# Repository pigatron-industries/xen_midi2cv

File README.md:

# MIDI - CV

MIDI to control voltage converter.

Uses [PJRC Teensy 4.0](https://www.pjrc.com/teensy-4-0/) and [MikroElektronika PIXI Click](https://www.mikroe.com/pixi-click) for IO.

## Hardware

Hardware functions are split into various PCBs.

* PGTNX05 Mainboard - Contains the Teensy 4 CPU, 2x MIDI Inputs and Outputs, 1x PIXI Click for 20 CV Outputs (12-bit).
* PGTNX06 IO Expander - Space for another 2x PIXI Click boards for up to 40 CV inputs or outputs.
* PGTNX07 Gate Output - 32x Gate/Trigger outputs.
* PGTNX08 Pitch Output - 8x 16-bit CV outputs for 1v/oct pitch control.

## Features

* 8 output channels each giving a Gate, Trigger, Pitch, Velocity and 2 Control Change outputs.
* Can be configured for a single MIDI channel to be mapped to multiple output channels for polyphonic operation.
* 8 separate percussion channel outputs with Trigger, and 2 Control Change outputs each, which can be mapped to individual notes on a single MIDI channel.

## Compiling

### Protobuf

Protobuf is used as a lightweight way of sending configuration data over midi sysex messages. The format of the message is specified in protobuf/ConfigMessage.proto.

If any changes are made to the format, the .c and .h files in the protobuf folder will need to be regenerated using the protobuf compiler.

This can be installed on Mac using the following commands:

`brew install protobuf`

`brew install nanopb-generator`

Then running the build.sh script will do the compilation.

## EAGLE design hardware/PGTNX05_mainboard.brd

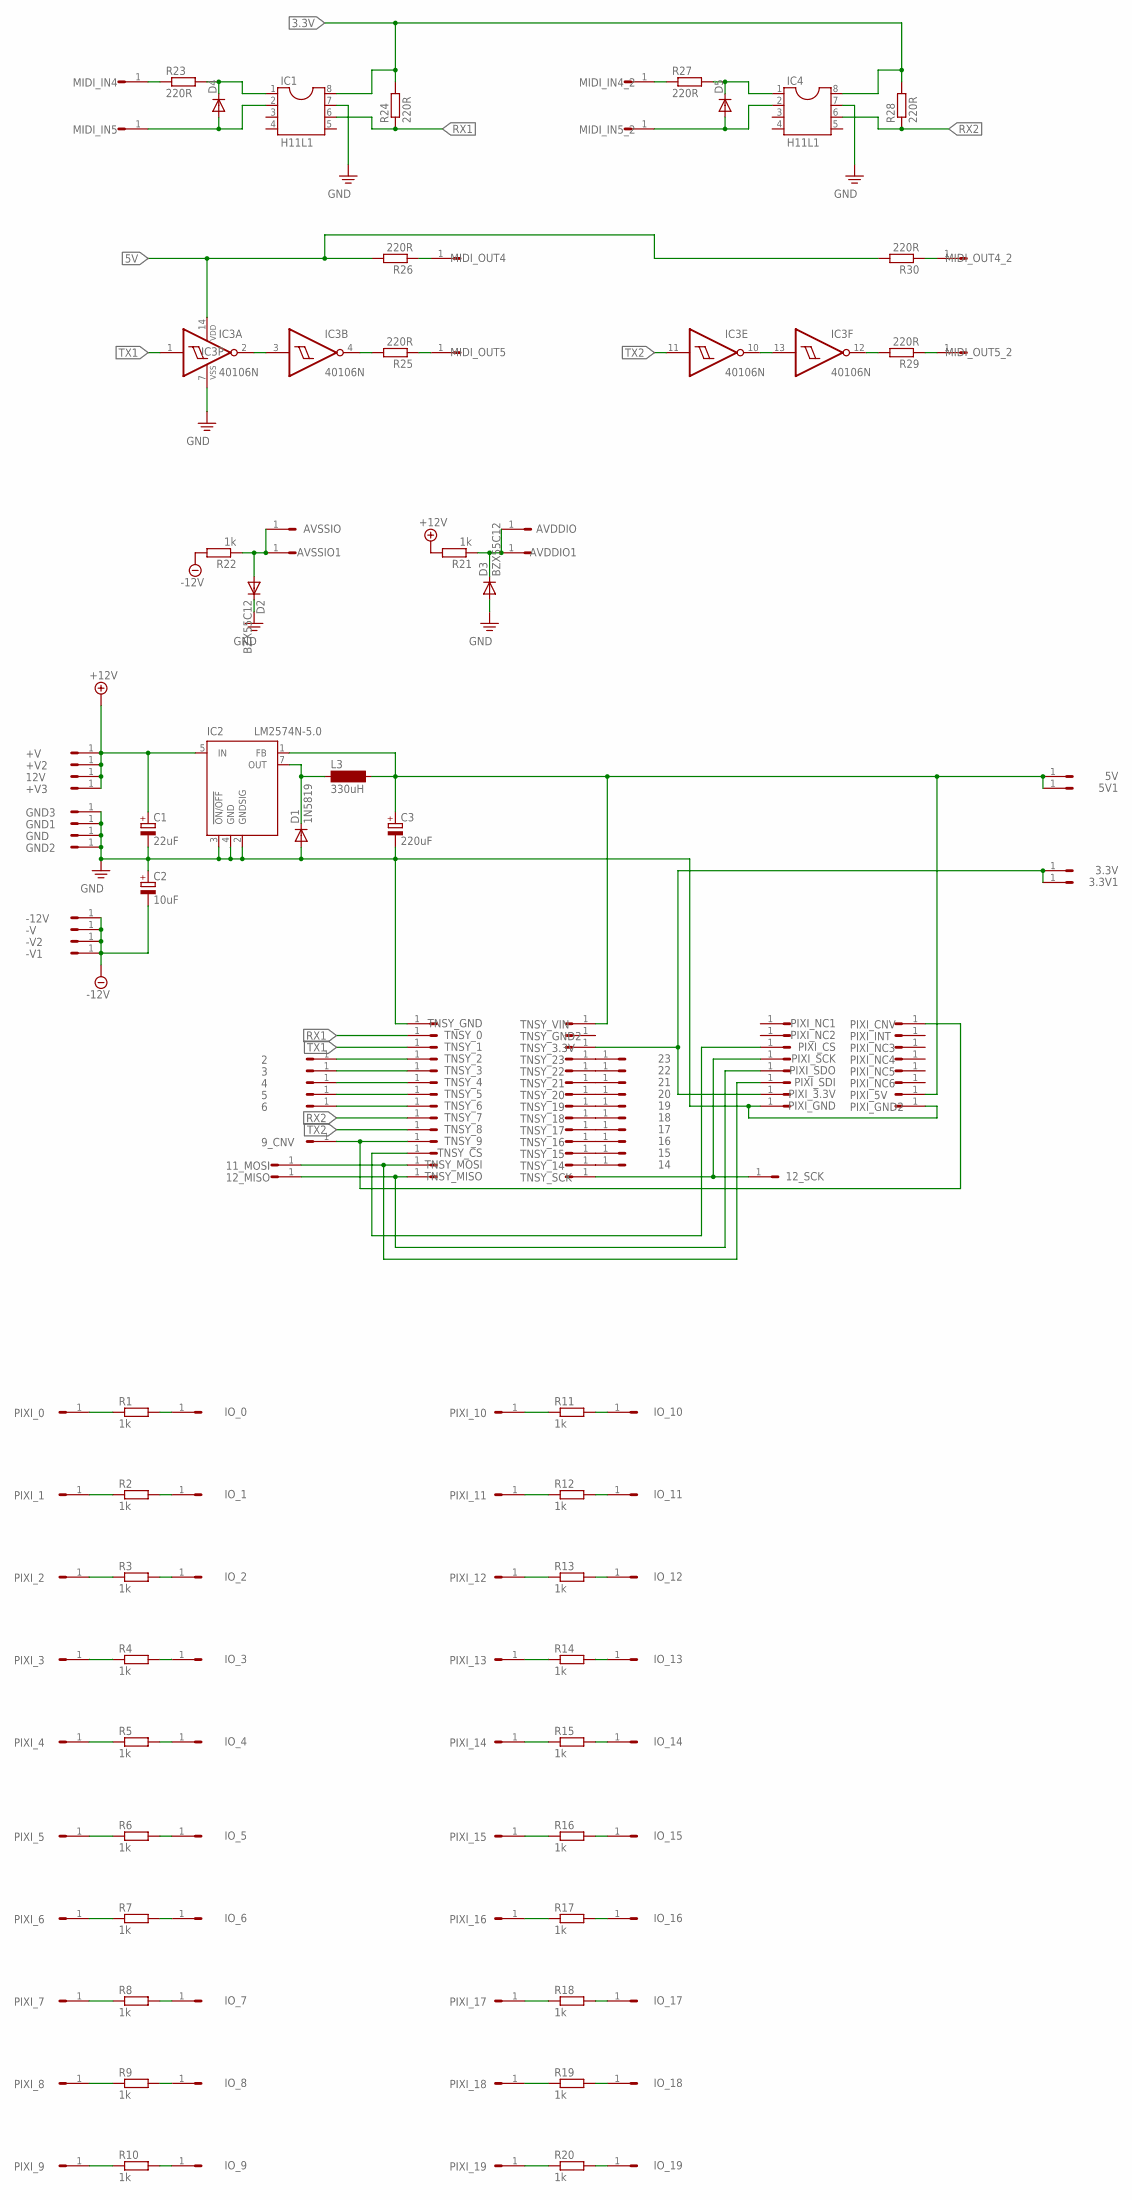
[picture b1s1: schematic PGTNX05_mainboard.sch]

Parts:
2, 3, 3.3V, 3.3V1, 4, 5, 5V, 5V1, 6, 9_CNV, 11_MOSI, 12V, 12_MISO, 12_SCK, 14, 15, 16, 17, 18, 19, 20, 21, 22, 23: HEADER/MALE/01
+V, +V2, +V3: HEADER/MALE/01
-12V: HEADER/MALE/01
-V, -V1, -V2: HEADER/MALE/01
AVDDIO, AVDDIO1: HEADER/MALE/01
AVSSIO, AVSSIO1: HEADER/MALE/01
C1: 22uF; E5-10,5
C2: 10uF; E2,5-6
C3: 220uF; E2,5-6
D1: 1N5819; DO35-7
D2, D3: BZX55C12; DO35-7
D4, D5: 1N4148DO35-7; DO35-7
GND, GND1, GND2, GND3: HEADER/MALE/01
IC1, IC4: H11L1; DIL08
IC2: LM2574N-5.0; DIL08
IC3: 40106N; DIL14
IO_0, IO_1, IO_2, IO_3, IO_4, IO_5, IO_6, IO_7, IO_8, IO_9, IO_10, IO_11, IO_12, IO_13, IO_14, IO_15, IO_16, IO_17, IO_18, IO_19: HEADER/MALE/01
L3: 330uH; BS11
MIDI_IN4, MIDI_IN4_2, MIDI_IN5, MIDI_IN5_2: HEADER/MALE/01
MIDI_OUT4, MIDI_OUT4_2, MIDI_OUT5, MIDI_OUT5_2: HEADER/MALE/01
PIXI_0, PIXI_1, PIXI_2, PIXI_3, PIXI_3.3V, PIXI_4, PIXI_5, PIXI_5V, PIXI_6, PIXI_7, PIXI_8, PIXI_9, PIXI_10, PIXI_11, PIXI_12, PIXI_13, PIXI_14, PIXI_15, PIXI_16, PIXI_17, PIXI_18, PIXI_19: HEADER/MALE/01
PIXI_CNV: HEADER/MALE/01
PIXI_CS: HEADER/MALE/01
PIXI_GND, PIXI_GND2: HEADER/MALE/01
PIXI_INT: HEADER/MALE/01
PIXI_NC1, PIXI_NC2, PIXI_NC3, PIXI_NC4, PIXI_NC5, PIXI_NC6: HEADER/MALE/01
PIXI_SCK: HEADER/MALE/01
PIXI_SDI: HEADER/MALE/01
PIXI_SDO: HEADER/MALE/01
R1, R2, R3, R4, R5, R6, R7, R8, R9, R10, R11, R12, R13, R14, R15, R16, R17, R18, R19, R20, R21, R22: 1k; RESISTOR/7.5
R23, R24, R25, R26, R27, R28, R29, R30: 220R; RESISTOR/7.5
TNSY_0, TNSY_1, TNSY_2, TNSY_3, TNSY_3.3V, TNSY_4, TNSY_5, TNSY_6, TNSY_7, TNSY_8, TNSY_9, TNSY_14, TNSY_15, TNSY_16, TNSY_17, TNSY_18, TNSY_19, TNSY_20, TNSY_21, TNSY_22, TNSY_23: HEADER/MALE/01
TNSY_CS: HEADER/MALE/01
TNSY_GND, TNSY_GND2: HEADER/MALE/01
TNSY_MISO: HEADER/MALE/01
TNSY_MOSI: HEADER/MALE/01
TNSY_SCK: HEADER/MALE/01
TNSY_VIN: HEADER/MALE/01

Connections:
3.3V: 3.3V.1, 3.3V1.1, IC1.8, IC4.8, PIXI_3.3V.1, R24.2, R28.2, TNSY_3.3V.1
5V: 5V.1, 5V1.1, C3.+, IC2.1 (FB), IC3.14 (VDD), L3.2, PIXI_5V.1, R26.2, R30.2, TNSY_VIN.1
+12V: 12V.1, +V.1, +V2.1, +V3.1, C1.+, IC2.5 (IN), R21.2
-12V: -12V.1, -V.1, -V1.1, -V2.1, C2.-, R22.2
GND: C1.-, C2.+, C3.-, D1.A, D2.C, D3.A, GND.1, GND1.1, GND2.1, GND3.1, IC1.7, IC2.2 (GNDSIG), IC2.3 (!ON/OFF), IC2.4 (GND), IC3.7 (VSS), IC4.7, PIXI_GND.1, PIXI_GND2.1, TNSY_GND.1
unnamed: 17.1, TNSY_17.1
unnamed: 16.1, TNSY_16.1
unnamed: D1.C, IC2.7 (OUT), L3.1
unnamed: 12_MISO.1, PIXI_SDO.1, TNSY_MISO.1
unnamed: PIXI_CS.1, TNSY_CS.1
unnamed: 18.1, TNSY_18.1
unnamed: 19.1, TNSY_19.1
unnamed: 20.1, TNSY_20.1
unnamed: 21.1, TNSY_21.1
unnamed: 22.1, TNSY_22.1
unnamed: 23.1, TNSY_23.1
unnamed: 15.1, TNSY_15.1
unnamed: 2.1, TNSY_2.1
unnamed: 3.1, TNSY_3.1
unnamed: 4.1, TNSY_4.1
unnamed: 5.1, TNSY_5.1
unnamed: PIXI_0.1, R1.1
unnamed: IO_0.1, R1.2
unnamed: PIXI_1.1, R2.1
unnamed: 6.1, TNSY_6.1
unnamed: IO_1.1, R2.2
unnamed: 9_CNV.1, PIXI_CNV.1, TNSY_9.1
unnamed: 11_MOSI.1, PIXI_SDI.1, TNSY_MOSI.1
unnamed: PIXI_2.1, R3.1
unnamed: 12_SCK.1, PIXI_SCK.1, TNSY_SCK.1
unnamed: 14.1, TNSY_14.1
unnamed: IO_2.1, R3.2
unnamed: PIXI_3.1, R4.1
unnamed: IO_3.1, R4.2
unnamed: PIXI_4.1, R5.1
unnamed: IO_4.1, R5.2
unnamed: PIXI_5.1, R6.1
unnamed: IO_5.1, R6.2
unnamed: PIXI_6.1, R7.1
unnamed: IO_6.1, R7.2
unnamed: PIXI_7.1, R8.1
unnamed: IO_7.1, R8.2
unnamed: PIXI_8.1, R9.1
unnamed: IO_8.1, R9.2
unnamed: PIXI_9.1, R10.1
unnamed: IO_9.1, R10.2
unnamed: PIXI_10.1, R11.1
unnamed: IO_10.1, R11.2
unnamed: PIXI_11.1, R12.1
unnamed: IO_11.1, R12.2
unnamed: PIXI_12.1, R13.1
unnamed: IO_12.1, R13.2
unnamed: PIXI_13.1, R14.1
unnamed: IO_13.1, R14.2
unnamed: PIXI_14.1, R15.1
unnamed: IO_14.1, R15.2
unnamed: PIXI_15.1, R16.1
unnamed: IO_15.1, R16.2
unnamed: PIXI_16.1, R17.1
unnamed: IO_16.1, R17.2
unnamed: PIXI_17.1, R18.1
unnamed: IO_17.1, R18.2
unnamed: PIXI_18.1, R19.1
unnamed: IO_18.1, R19.2
unnamed: AVDDIO.1, AVDDIO1.1, D3.C, R21.1
unnamed: AVSSIO.1, AVSSIO1.1, D2.A, R22.1
unnamed: PIXI_19.1, R20.1
unnamed: IO_19.1, R20.2
unnamed: MIDI_IN4.1, R23.1
unnamed: D4.C, IC1.1, R23.2
unnamed: D4.A, IC1.2, MIDI_IN5.1
unnamed: IC3.2 (O), IC3.3 (I)
unnamed: IC3.4 (O), R25.2
unnamed: MIDI_OUT5.1, R25.1
unnamed: MIDI_OUT4.1, R26.1
unnamed: MIDI_IN4_2.1, R27.1
unnamed: D5.C, IC4.1, R27.2
unnamed: D5.A, IC4.2, MIDI_IN5_2.1
unnamed: IC3.10 (O), IC3.13 (I)
unnamed: IC3.12 (O), R29.2
unnamed: MIDI_OUT5_2.1, R29.1
unnamed: MIDI_OUT4_2.1, R30.1
RX1: IC1.6, R24.1, TNSY_0.1
RX2: IC4.6, R28.1, TNSY_7.1
TX1: IC3.1 (I), TNSY_1.1
TX2: IC3.11 (I), TNSY_8.1

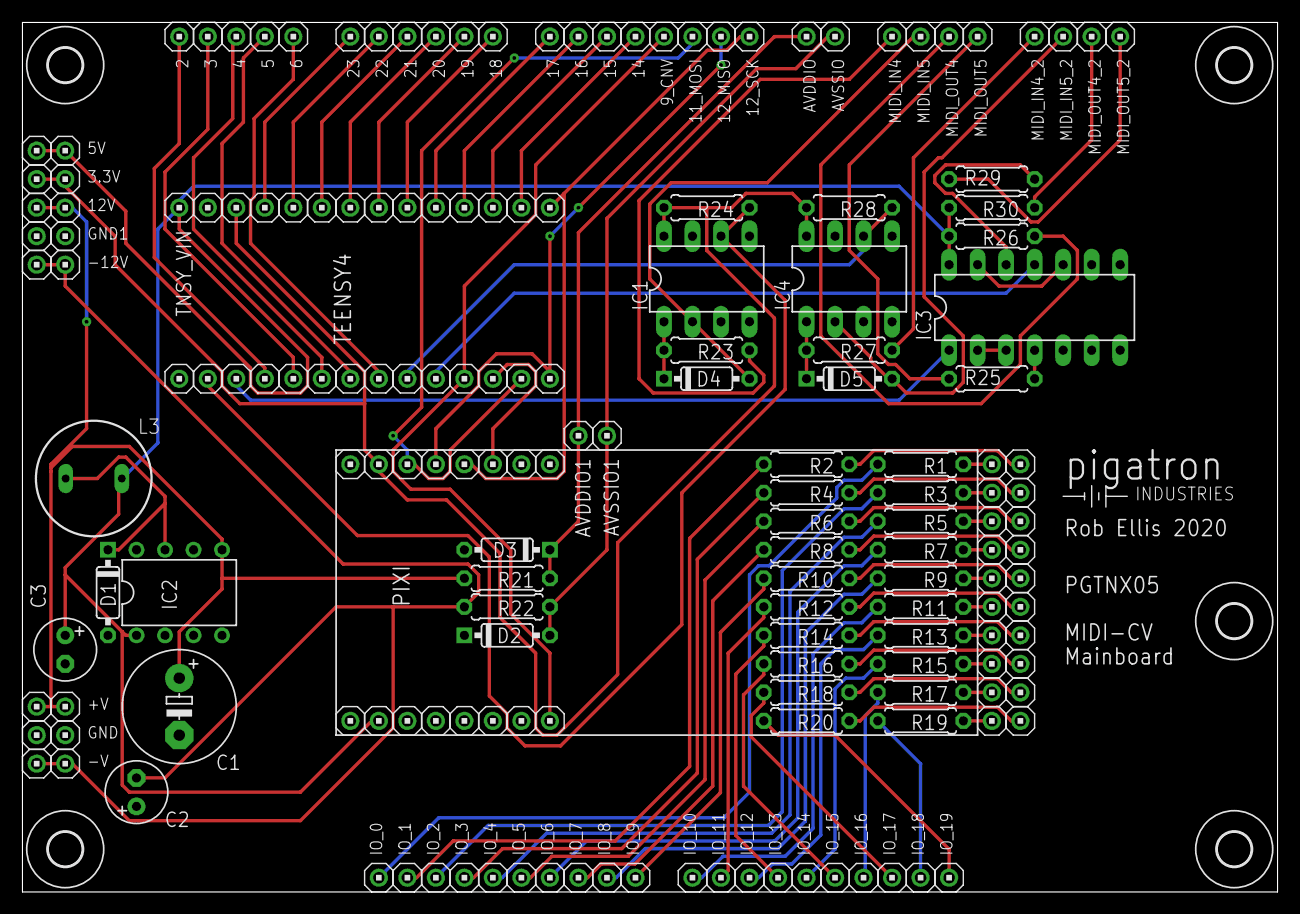
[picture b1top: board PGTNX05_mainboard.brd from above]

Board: 2 copper layers, 111.8 x 77.5 mm, 180 parts (0 on the bottom side), 86 nets.

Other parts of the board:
U$1, U$2, U$3, U$4, U$7: STANDOFF/3.0
U$5: PIGATRON-LOGO

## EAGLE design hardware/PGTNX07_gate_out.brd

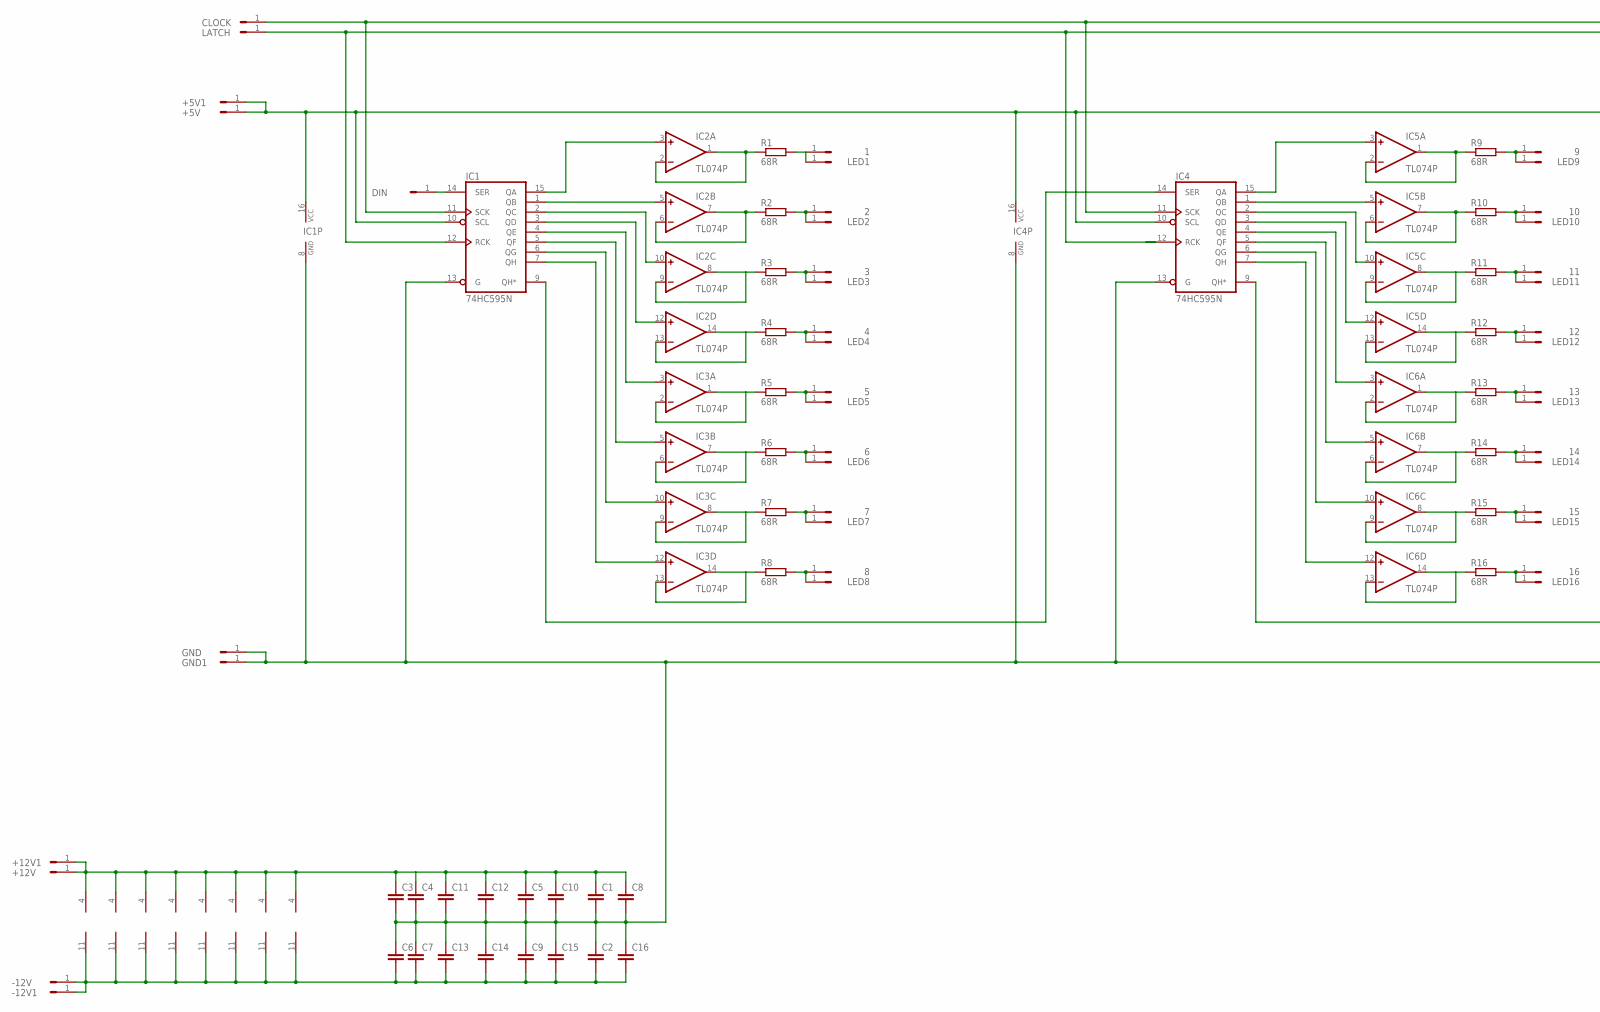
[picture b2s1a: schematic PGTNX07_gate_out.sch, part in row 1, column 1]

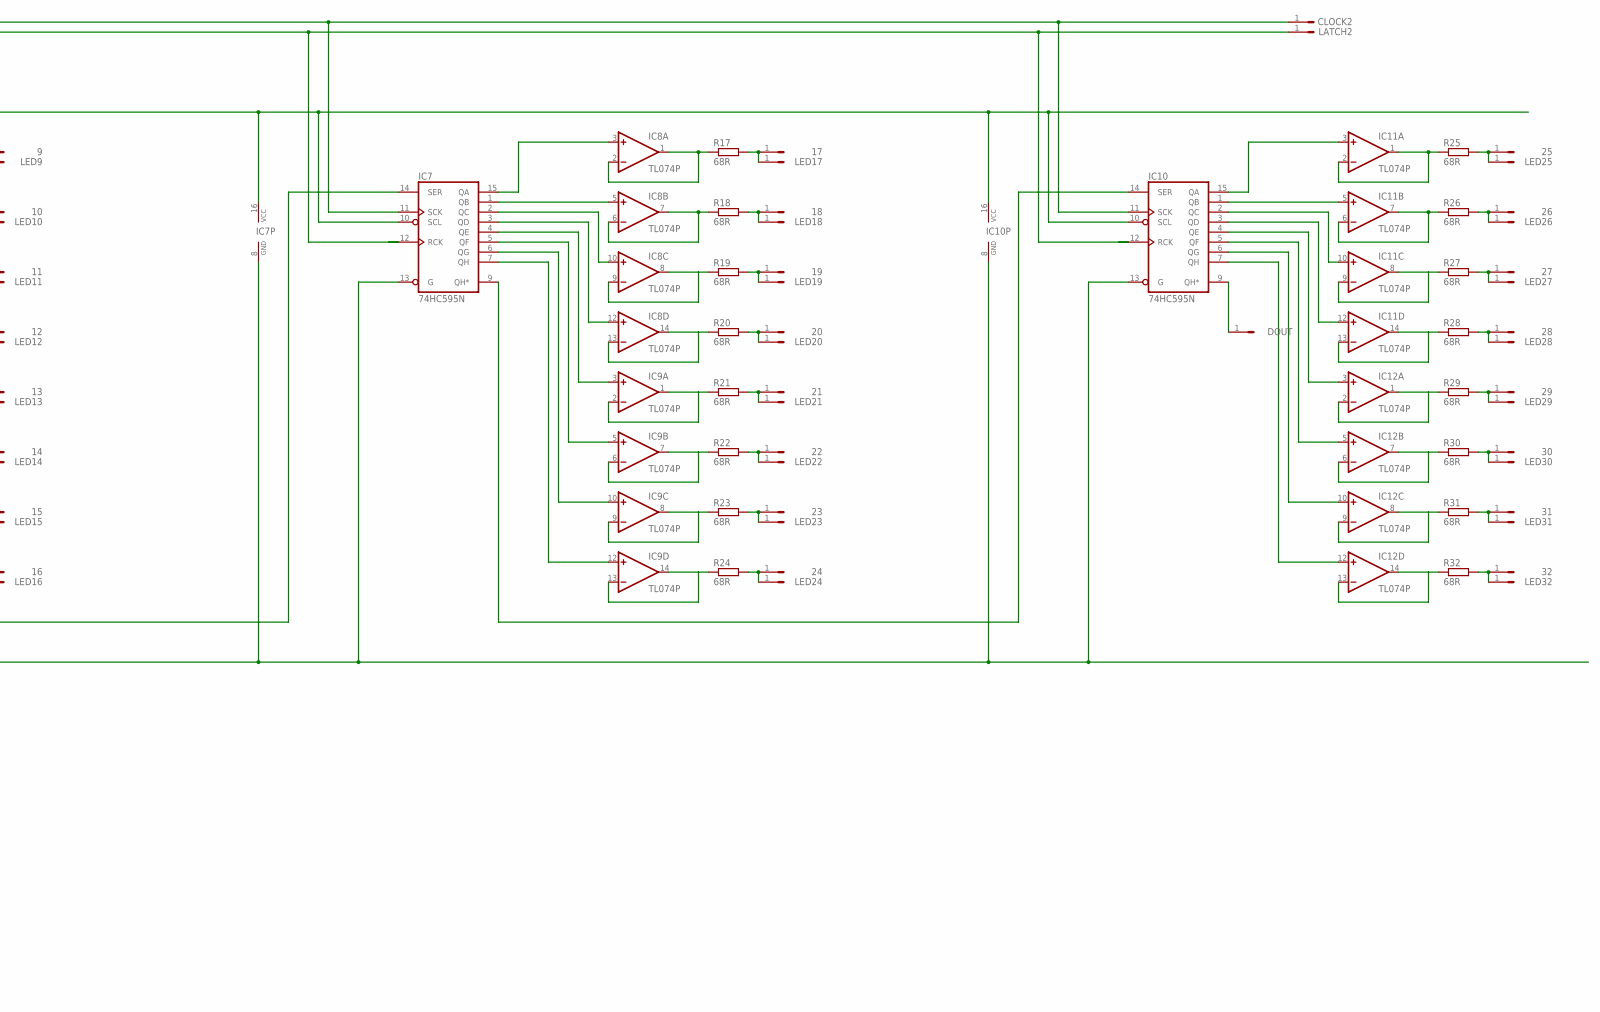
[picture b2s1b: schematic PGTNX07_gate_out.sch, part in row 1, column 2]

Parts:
1, 2, 3, 4, 5, 6, 7, 8, 9, 10, 11, 12, 13, 14, 15, 16, 17, 18, 19, 20, 21, 22, 23, 24, 25, 26, 27, 28, 29, 30, 31, 32: HEADER/MALE/01
+5V, +5V1, +12V, +12V1: HEADER/MALE/01
-12V, -12V1: HEADER/MALE/01
C1, C2, C3, C4, C5, C6, C7, C8, C9, C10, C11, C12, C13, C14, C15, C16: CAPACITORCERAMICDISC/5; CERAMICDISC/5
CLOCK, CLOCK2: HEADER/MALE/01
DIN: HEADER/MALE/01
DOUT: HEADER/MALE/01
GND, GND1: HEADER/MALE/01
IC1, IC4, IC7, IC10: 74HC595N; DIL16
IC2, IC3, IC5, IC6, IC8, IC9, IC11, IC12: TL074P; DIL14
LATCH, LATCH2: HEADER/MALE/01
LED1, LED2, LED3, LED4, LED5, LED6, LED7, LED8, LED9, LED10, LED11, LED12, LED13, LED14, LED15, LED16, LED17, LED18, LED19, LED20, LED21, LED22, LED23, LED24, LED25, LED26, LED27, LED28, LED29, LED30, LED31, LED32: HEADER/MALE/01
R1, R2, R3, R4, R5, R6, R7, R8, R9, R10, R11, R12, R13, R14, R15, R16, R17, R18, R19, R20, R21, R22, R23, R24, R25, R26, R27, R28, R29, R30, R31, R32: 68R; RESISTOR/7.5

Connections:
+5V: +5V.1, +5V1.1, IC1.10 (SCL), IC1.16 (VCC), IC4.10 (SCL), IC4.16 (VCC), IC7.10 (SCL), IC7.16 (VCC), IC10.10 (SCL), IC10.16 (VCC)
GND: C1.2, C2.1, C3.2, C4.2, C5.2, C6.1, C7.1, C8.2, C9.1, C10.2, C11.2, C12.2, C13.1, C14.1, C15.1, C16.1, GND.1, GND1.1, IC1.8 (GND), IC1.13 (G), IC4.8 (GND), IC4.13 (G), IC7.8 (GND), IC7.13 (G), IC10.8 (GND), IC10.13 (G)
unnamed: IC1.15 (QA), IC2.3 (+IN)
unnamed: IC1.1 (QB), IC2.5 (+IN)
unnamed: DIN.1, IC1.14 (SER)
unnamed: IC1.2 (QC), IC2.10 (+IN)
unnamed: IC1.3 (QD), IC2.12 (+IN)
unnamed: IC1.4 (QE), IC3.3 (+IN)
unnamed: IC1.5 (QF), IC3.5 (+IN)
unnamed: IC1.6 (QG), IC3.10 (+IN)
unnamed: IC1.7 (QH), IC3.12 (+IN)
unnamed: IC1.9 (QH*), IC4.14 (SER)
unnamed: IC2.1 (OUT), IC2.2 (-IN), R1.1
unnamed: 1.1, LED1.1, R1.2
unnamed: IC2.6 (-IN), IC2.7 (OUT), R2.1
unnamed: 2.1, LED2.1, R2.2
unnamed: +12V.1, +12V1.1, C1.1, C3.1, C4.1, C5.1, C8.1, C10.1, C11.1, C12.1, IC2.4 (V+), IC3.4 (V+), IC5.4 (V+), IC6.4 (V+), IC8.4 (V+), IC9.4 (V+), IC11.4 (V+), IC12.4 (V+)
unnamed: -12V.1, -12V1.1, C2.2, C6.2, C7.2, C9.2, C13.2, C14.2, C15.2, C16.2, IC2.11 (V-), IC3.11 (V-), IC5.11 (V-), IC6.11 (V-), IC8.11 (V-), IC9.11 (V-), IC11.11 (V-), IC12.11 (V-)
unnamed: CLOCK.1, CLOCK2.1, IC1.11 (SCK), IC4.11 (SCK), IC7.11 (SCK), IC10.11 (SCK)
unnamed: IC2.8 (OUT), IC2.9 (-IN), R3.1
unnamed: IC2.13 (-IN), IC2.14 (OUT), R4.1
unnamed: IC3.1 (OUT), IC3.2 (-IN), R5.1
unnamed: IC3.6 (-IN), IC3.7 (OUT), R6.1
unnamed: IC3.8 (OUT), IC3.9 (-IN), R7.1
unnamed: IC3.13 (-IN), IC3.14 (OUT), R8.1
unnamed: 3.1, LED3.1, R3.2
unnamed: 4.1, LED4.1, R4.2
unnamed: 5.1, LED5.1, R5.2
unnamed: 6.1, LED6.1, R6.2
unnamed: 7.1, LED7.1, R7.2
unnamed: 8.1, LED8.1, R8.2
unnamed: IC1.12 (RCK), IC4.12 (RCK), IC7.12 (RCK), IC10.12 (RCK), LATCH.1, LATCH2.1
unnamed: IC4.9 (QH*), IC7.14 (SER)
unnamed: IC4.2 (QC), IC5.10 (+IN)
unnamed: IC4.3 (QD), IC5.12 (+IN)
unnamed: IC4.4 (QE), IC6.3 (+IN)
unnamed: IC4.5 (QF), IC6.5 (+IN)
unnamed: IC4.6 (QG), IC6.10 (+IN)
unnamed: IC4.15 (QA), IC5.3 (+IN)
unnamed: IC4.1 (QB), IC5.5 (+IN)
unnamed: IC4.7 (QH), IC6.12 (+IN)
unnamed: IC5.1 (OUT), IC5.2 (-IN), R9.1
unnamed: 9.1, LED9.1, R9.2
unnamed: IC5.6 (-IN), IC5.7 (OUT), R10.1
unnamed: 10.1, LED10.1, R10.2
unnamed: IC7.9 (QH*), IC10.14 (SER)
unnamed: IC7.2 (QC), IC8.10 (+IN)
unnamed: IC5.8 (OUT), IC5.9 (-IN), R11.1
unnamed: IC5.13 (-IN), IC5.14 (OUT), R12.1
unnamed: IC6.1 (OUT), IC6.2 (-IN), R13.1
unnamed: IC6.6 (-IN), IC6.7 (OUT), R14.1
unnamed: IC6.8 (OUT), IC6.9 (-IN), R15.1
unnamed: IC6.13 (-IN), IC6.14 (OUT), R16.1
unnamed: 11.1, LED11.1, R11.2
unnamed: 12.1, LED12.1, R12.2
unnamed: 13.1, LED13.1, R13.2
unnamed: 14.1, LED14.1, R14.2
unnamed: 15.1, LED15.1, R15.2
unnamed: 16.1, LED16.1, R16.2
unnamed: IC7.3 (QD), IC8.12 (+IN)
unnamed: IC7.4 (QE), IC9.3 (+IN)
unnamed: IC7.5 (QF), IC9.5 (+IN)
unnamed: IC7.6 (QG), IC9.10 (+IN)
unnamed: IC7.15 (QA), IC8.3 (+IN)
unnamed: IC7.1 (QB), IC8.5 (+IN)
unnamed: IC7.7 (QH), IC9.12 (+IN)
unnamed: IC8.1 (OUT), IC8.2 (-IN), R17.1
unnamed: 17.1, LED17.1, R17.2
unnamed: IC8.6 (-IN), IC8.7 (OUT), R18.1
unnamed: 18.1, LED18.1, R18.2
unnamed: IC8.8 (OUT), IC8.9 (-IN), R19.1
unnamed: IC8.13 (-IN), IC8.14 (OUT), R20.1
unnamed: IC9.1 (OUT), IC9.2 (-IN), R21.1
unnamed: IC9.6 (-IN), IC9.7 (OUT), R22.1
unnamed: IC9.8 (OUT), IC9.9 (-IN), R23.1
unnamed: IC9.13 (-IN), IC9.14 (OUT), R24.1
unnamed: 19.1, LED19.1, R19.2
unnamed: 20.1, LED20.1, R20.2
unnamed: 21.1, LED21.1, R21.2
unnamed: 22.1, LED22.1, R22.2
unnamed: 23.1, LED23.1, R23.2
unnamed: 24.1, LED24.1, R24.2
unnamed: DOUT.1, IC10.9 (QH*)
unnamed: IC10.2 (QC), IC11.10 (+IN)
unnamed: IC10.3 (QD), IC11.12 (+IN)
unnamed: IC10.4 (QE), IC12.3 (+IN)
unnamed: IC10.5 (QF), IC12.5 (+IN)
unnamed: IC10.6 (QG), IC12.10 (+IN)
unnamed: IC10.15 (QA), IC11.3 (+IN)
unnamed: IC10.1 (QB), IC11.5 (+IN)
unnamed: IC10.7 (QH), IC12.12 (+IN)
unnamed: IC11.1 (OUT), IC11.2 (-IN), R25.1
unnamed: 25.1, LED25.1, R25.2
unnamed: IC11.6 (-IN), IC11.7 (OUT), R26.1
unnamed: 26.1, LED26.1, R26.2
unnamed: IC11.8 (OUT), IC11.9 (-IN), R27.1
unnamed: IC11.13 (-IN), IC11.14 (OUT), R28.1
unnamed: IC12.1 (OUT), IC12.2 (-IN), R29.1
unnamed: IC12.6 (-IN), IC12.7 (OUT), R30.1
unnamed: IC12.8 (OUT), IC12.9 (-IN), R31.1
unnamed: IC12.13 (-IN), IC12.14 (OUT), R32.1
unnamed: 27.1, LED27.1, R27.2
unnamed: 28.1, LED28.1, R28.2
unnamed: 29.1, LED29.1, R29.2
unnamed: 30.1, LED30.1, R30.2
unnamed: 31.1, LED31.1, R31.2
unnamed: 32.1, LED32.1, R32.2

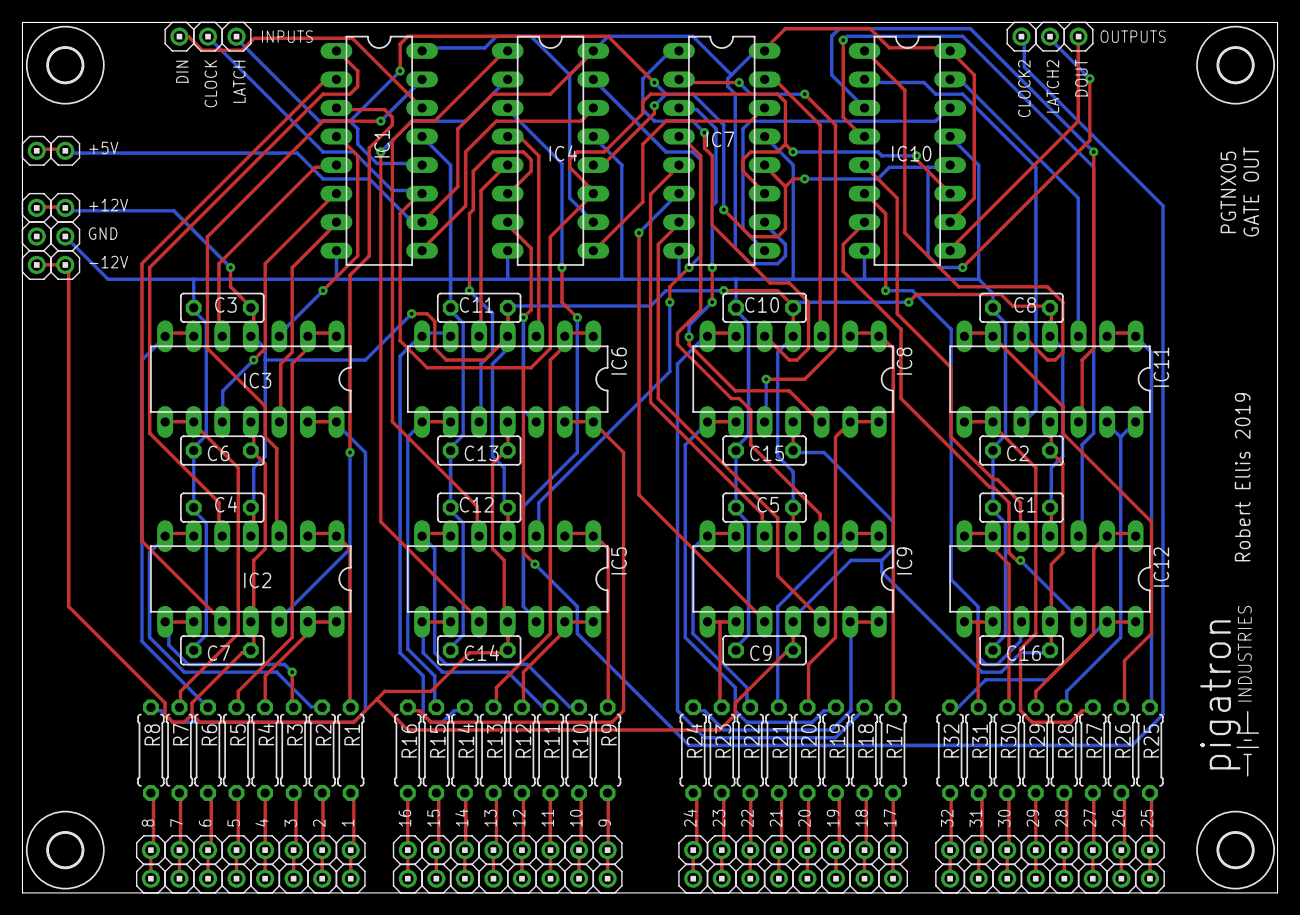
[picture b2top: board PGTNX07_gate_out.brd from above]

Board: 2 copper layers, 111.7 x 77.5 mm, 143 parts (0 on the bottom side), 107 nets.

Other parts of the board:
U$1, U$2, U$3, U$4: STANDOFF/3.0
U$5: PIGATRON-LOGO

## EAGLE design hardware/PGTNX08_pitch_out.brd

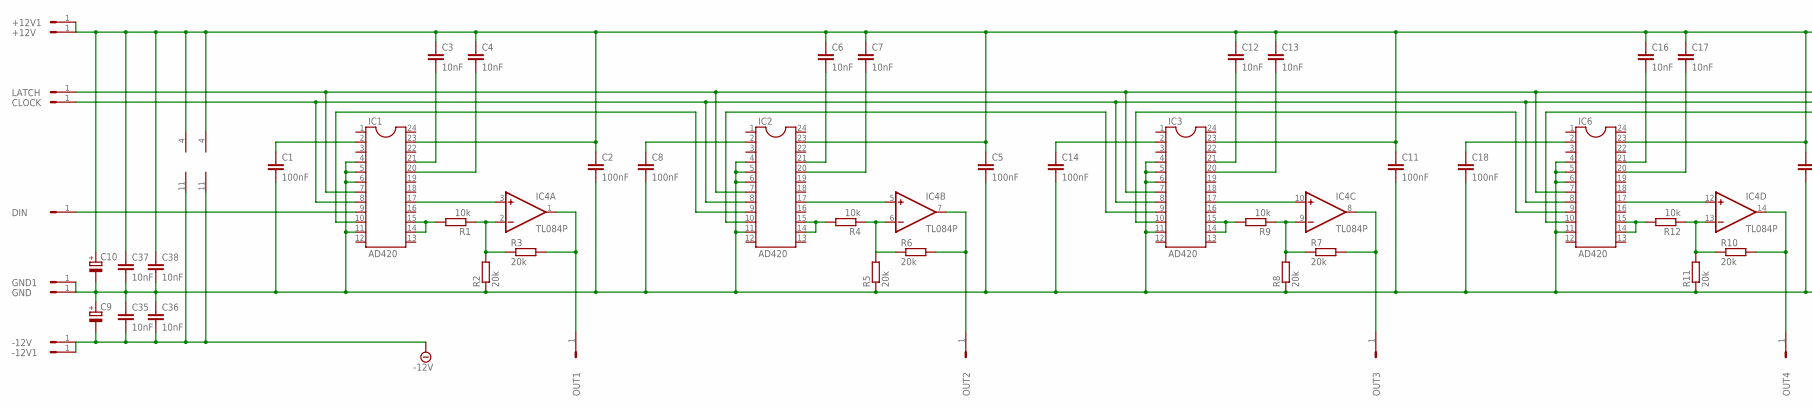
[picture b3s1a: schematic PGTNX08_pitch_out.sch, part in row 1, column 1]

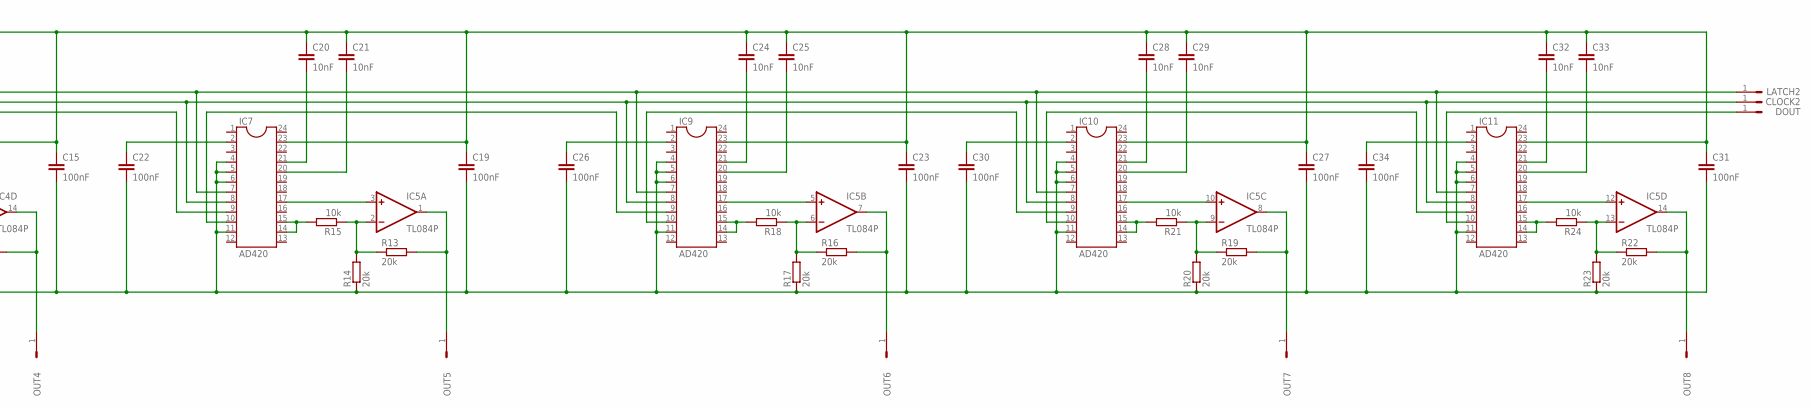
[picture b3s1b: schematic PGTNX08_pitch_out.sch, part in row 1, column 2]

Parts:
+12V, +12V1: HEADER/MALE/01
-12V, -12V1: HEADER/MALE/01
C1, C2, C5, C8, C11, C14, C15, C18, C19, C22, C23, C26, C27, C30, C31, C34: 100nF; CERAMICDISC/5
C3, C4, C6, C7, C12, C13, C16, C17, C20, C21, C24, C25, C28, C29, C32, C33, C35, C36, C37, C38: 10nF; CERAMICDISC/5
C9, C10: CAPACITOR/POLARIZEDE2.5-6; E2,5-6
CLOCK, CLOCK2: HEADER/MALE/01
DIN: HEADER/MALE/01
DOUT: HEADER/MALE/01
GND, GND1: HEADER/MALE/01
IC1, IC2, IC3, IC6, IC7, IC9, IC10, IC11: AD420; DIL24-3
IC4, IC5: TL084P; DIL14
LATCH, LATCH2: HEADER/MALE/01
OUT1, OUT2, OUT3, OUT4, OUT5, OUT6, OUT7, OUT8: HEADER/MALE/01
R1, R4: 10k; 0204/7
R2, R5: 20k; 0204/7
R3, R6, R7, R8, R10, R11, R13, R14, R16, R17, R19, R20, R22, R23: 20k; RESISTOR/7.5
R9, R12, R15, R18, R21, R24: 10k; RESISTOR/7.5

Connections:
+12V: +12V.1, +12V1.1, C2.1, C3.1, C4.1, C5.1, C6.1, C7.1, C10.+, C11.1, C12.1, C13.1, C15.1, C16.1, C17.1, C19.1, C20.1, C21.1, C23.1, C24.1, C25.1, C27.1, C28.1, C29.1, C31.1, C32.1, C33.1, C37.1, C38.1, IC1.23, IC2.23, IC3.23, IC4.4 (V+), IC5.4 (V+), IC6.23, IC7.23, IC9.23, IC10.23, IC11.23
-12V: -12V.1, -12V1.1, C9.-, C35.2, C36.2, IC4.11 (V-), IC5.11 (V-)
GND: C1.2, C2.2, C5.2, C8.2, C9.+, C10.-, C11.2, C14.2, C15.2, C18.2, C19.2, C22.2, C23.2, C26.2, C27.2, C30.2, C31.2, C34.2, C35.1, C36.1, C37.2, C38.2, GND.1, GND1.1, IC1.4, IC1.5, IC1.6, IC1.11, IC2.4, IC2.5, IC2.6, IC2.11, IC3.4, IC3.5, IC3.6, IC3.11, IC6.4, IC6.5, IC6.6, IC6.11, IC7.4, IC7.5, IC7.6, IC7.11, IC9.4, IC9.5, IC9.6, IC9.11, IC10.4, IC10.5, IC10.6, IC10.11, IC11.4, IC11.5, IC11.6, IC11.11, R2.1, R5.1, R8.1, R11.1, R14.1, R17.1, R20.1, R23.1
unnamed: IC3.10, IC6.9
unnamed: IC6.10, IC7.9
unnamed: DIN.1, IC1.9
unnamed: IC2.14, IC2.15, R4.2
unnamed: IC2.10, IC3.9
unnamed: IC4.2 (-IN), R1.1, R2.2, R3.1
unnamed: IC9.10, IC10.9
unnamed: C1.1, IC1.2
unnamed: C3.2, IC1.21
unnamed: C4.2, IC1.20
unnamed: IC1.17, IC4.3 (+IN)
unnamed: IC1.14, IC1.15, R1.2
unnamed: IC4.1 (OUT), OUT1.1, R3.2
unnamed: IC7.10, IC9.9
unnamed: IC1.10, IC2.9
unnamed: IC2.17, IC4.5 (+IN)
unnamed: IC4.7 (OUT), OUT2.1, R6.2
unnamed: IC3.14, IC3.15, R9.2
unnamed: C8.1, IC2.2
unnamed: C6.2, IC2.21
unnamed: C7.2, IC2.20
unnamed: IC4.6 (-IN), R4.1, R5.2, R6.1
unnamed: IC3.17, IC4.10 (+IN)
unnamed: IC4.8 (OUT), OUT3.1, R7.2
unnamed: C14.1, IC3.2
unnamed: C12.2, IC3.21
unnamed: C13.2, IC3.20
unnamed: IC10.10, IC11.9
unnamed: IC4.9 (-IN), R7.1, R8.2, R9.1
unnamed: IC6.14, IC6.15, R12.2
unnamed: IC4.12 (+IN), IC6.17
unnamed: IC4.14 (OUT), OUT4.1, R10.2
unnamed: C18.1, IC6.2
unnamed: C16.2, IC6.21
unnamed: C17.2, IC6.20
unnamed: CLOCK.1, CLOCK2.1, IC1.8, IC2.8, IC3.8, IC6.8, IC7.8, IC9.8, IC10.8, IC11.8
unnamed: IC4.13 (-IN), R10.1, R11.2, R12.1
unnamed: IC7.14, IC7.15, R15.2
unnamed: IC5.3 (+IN), IC7.17
unnamed: IC5.1 (OUT), OUT5.1, R13.2
unnamed: C22.1, IC7.2
unnamed: C20.2, IC7.21
unnamed: C21.2, IC7.20
unnamed: IC5.2 (-IN), R13.1, R14.2, R15.1
unnamed: IC9.14, IC9.15, R18.2
unnamed: IC5.5 (+IN), IC9.17
unnamed: IC5.7 (OUT), OUT6.1, R16.2
unnamed: C26.1, IC9.2
unnamed: C24.2, IC9.21
unnamed: C25.2, IC9.20
unnamed: DOUT.1, IC11.10
unnamed: IC5.6 (-IN), R16.1, R17.2, R18.1
unnamed: IC10.14, IC10.15, R21.2
unnamed: IC5.10 (+IN), IC10.17
unnamed: IC5.8 (OUT), OUT7.1, R19.2
unnamed: C30.1, IC10.2
unnamed: C28.2, IC10.21
unnamed: C29.2, IC10.20
unnamed: IC5.9 (-IN), R19.1, R20.2, R21.1
unnamed: IC11.14, IC11.15, R24.2
unnamed: IC5.12 (+IN), IC11.17
unnamed: IC5.14 (OUT), OUT8.1, R22.2
unnamed: C34.1, IC11.2
unnamed: C32.2, IC11.21
unnamed: C33.2, IC11.20
unnamed: IC1.7, IC2.7, IC3.7, IC6.7, IC7.7, IC9.7, IC10.7, IC11.7, LATCH.1, LATCH2.1
unnamed: IC5.13 (-IN), R22.1, R23.2, R24.1

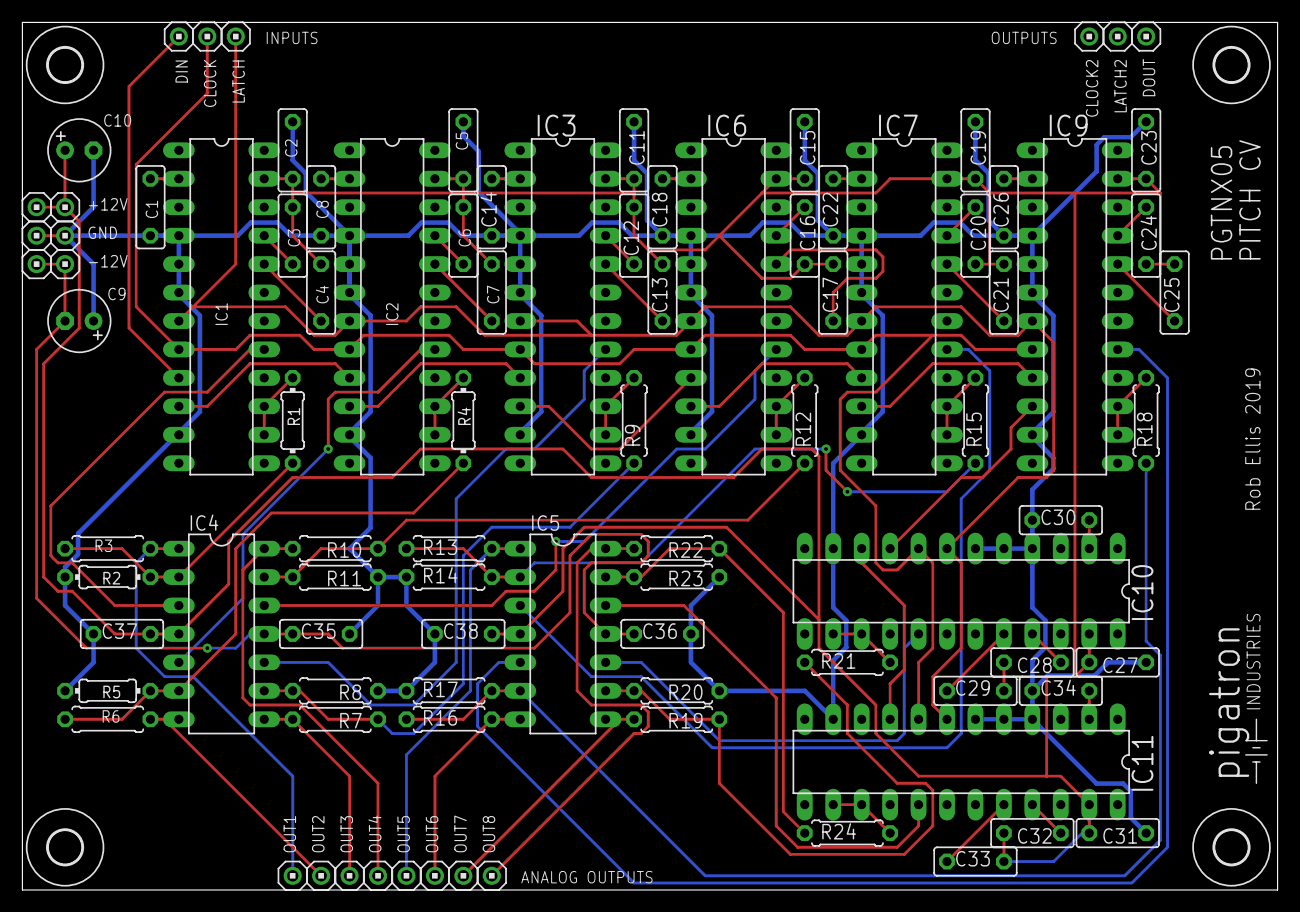
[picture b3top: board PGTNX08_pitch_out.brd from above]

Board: 2 copper layers, 112.1 x 77.5 mm, 97 parts (0 on the bottom side), 70 nets.

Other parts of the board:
U$1, U$2, U$3, U$4: 3,0
U$5: PIGATRON-LOGO

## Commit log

2019-09-29 A lot of code to just blink a blue led
2019-10-05 Added 3 status leds + midi input task
2019-10-05 Fixed compile error and added serial output for debugging
2019-10-06 Read MIDI data from Serial2
2019-10-11 Pitch CV Dac driver
2019-10-13 Added MidiEventProcessor
2019-10-13 Added parameters to note on and note off functions
2019-10-13 Renqmed PitchCvDac to PitchCvOutput
2019-10-16 Add configuration object
2019-10-17 Made types consistent
2019-10-17 Add midi channel mappings to configuration object
2019-10-18 Gate outputs
2019-10-18 made datatypes consistent
2019-10-18 convert midi chanel to cv channel and rotate
2019-10-18 chnaged datatype to match constructor
2019-10-19 get channel for note off event
2019-10-19 Add set data and send method to gate output
2019-10-19 added xendData function to gate output
2019-10-19 Fixed issues after hardware testing. Handle midi messages longer than 3 bytes
2019-10-19 added function turn save and clear notes to channels
2019-10-19 save list of notes to channel when multiple notes are held down
2019-10-19 Don't save duplicate notes to channel
2019-10-20 Handle system messages
2019-10-20 Connected up pitch cv
2019-10-22 initialise variable
2019-10-25 Read in sysex messages
2019-10-26 Decode sysex messages in base64
2019-10-26 Added protobuf for configurtion message
2019-10-27 renamed WrapperMessage to ConfigWrapper
2019-10-27 Use protobuf object to store config
2019-10-27 Tidy up serial messasges
2019-10-27 Add scale to protobuf message
2019-10-27 Use configured scale to determine note pitches
2019-10-27 Read config message into second buffer to prevent overriting with partial messages
2019-10-27 changed to config reference
2019-10-29 removed unused defines
2019-10-29 add control change event
2019-10-29 added note pressure event
2019-10-30 Added pitch bend event
2019-11-02 constant for baud rates
2019-11-03 Implemented pitch bend
2019-11-05 Added trigger output task
2019-11-05 added trigger time to config object
2019-11-05 add triggerTime to config object
2019-11-05 Add trigger output hardware config
2019-11-05 Call trigger from midi note on
2019-11-06 Changed pins for trigger output
2019-11-06 Added MAX11300 library
2019-11-07 Implemented constructor for CvOutput
2019-11-07 added setValue function
2019-11-07 Added setVoltage function on cvOutput
2019-11-07 Fixed compile errors and added convertVelocity function
2019-11-07 set velocity on note on event
2019-11-10 Changed cv output pins
2019-11-14 Define cv config and percussion channel config
2019-11-15 Increase size of controller mapping field
2019-11-16 Add function to get cv controller mapping
2019-11-16 Added Cv Output service to wrap all output hardware
2019-11-16 Changes midi processor to use new cv output service
2019-11-16 define arrays statically
2019-11-16 moved cv output service to drivers
2019-11-16 moved midi processor to programs folder
2019-11-16 moved midi input task to midi prgogram folder
2019-11-16 changes ended to enabled to allow tasks to be turned on and off
2019-11-23 fixed enabled check
2019-11-23 channel pressure and program change don't have a 2nd data byte
2019-11-23 Fixed redeclaration of byte3
2019-12-03 Add percussion event to midi processor
2019-12-03 changed cv output service to use channel and bank instead of a single index
2019-12-03 Implemented note and channel pressure events
2019-12-03 Implemented controller change midi event. Split config up into channel and bank.
2019-12-03 Added coarse and fine control numbers. Changes int size of message to 8 bits.
2019-12-03 removed coarse and fone controller numbers, will handle as one
2019-12-07 Only send trigger data when something changed
2019-12-08 A few fixes to MAX11300 library (bit order wrong, read/write bit backwards, using conditional && instead of bitwise &, not setting select pin to output mode)
2019-12-08 Set DAC internal reference by default
2019-12-13 Wait until next byte before sending control change message in case there is a LSB control change message.
2019-12-22 Mefthod to convert control value to float
2019-12-22 Chnage trigger pins and percussion midi channel
2019-12-29 Allow differnt drum notes to trigger same drum with different control values
2019-12-29 Select device MAX11300 device based on index.
2019-12-29 chnage percussion mapping max count to 64
2020-01-10 Pass in HardwareSerial as paremter to MidiInputTask
2020-01-11 Instantiate second midi input
2020-01-19 Added 2 MIDI inputs and a MIDI output
2020-03-29 Moved hardware files to this project
2020-03-29 Tidy up scheamtics
2020-03-29 Added seperate headers for driving leds from outputs
2020-03-29 IO Expander PCB
2020-04-18 Added correct diode type BZX55C12
2020-04-18 Add resistor values
2020-04-19 Refactored code to work on Teensy 4.0 with new PCBs.
2020-04-21 added .gitattributes
2020-04-25 Made triggers work, only send data to output at the end of main loop
2020-05-09 Added clock output based on midi clock
2020-05-09 change int to unsigned
2020-05-09 Adde quarter note clock signal
2020-05-09 Reset clock counter on start and stop. All notes off on reset message
2020-05-10 Corrected reset function call
2020-05-16 Spelling mistake in comment
2020-06-04 Moved to platform IO project
2020-07-02 Correct teensy41 to teensy 40, fixed warning
2020-07-02 changed cv pin numbers to match hardware
2020-11-21 Added 3rd MidiInputTask Instance
2020-12-21 Pass through midi from input to output.
2020-12-21 Don't pass through to Serial3 if message came from Serial3
2020-12-22 Turn all notes off on stop message
2021-05-24 Fixed note off bug when two midi channels have same note on
2021-05-29 CHnaged pin numner and added some sample of polyphonic config
2021-05-30 Receive midi over USB
2021-06-20 Use second clock output for reset trigger
